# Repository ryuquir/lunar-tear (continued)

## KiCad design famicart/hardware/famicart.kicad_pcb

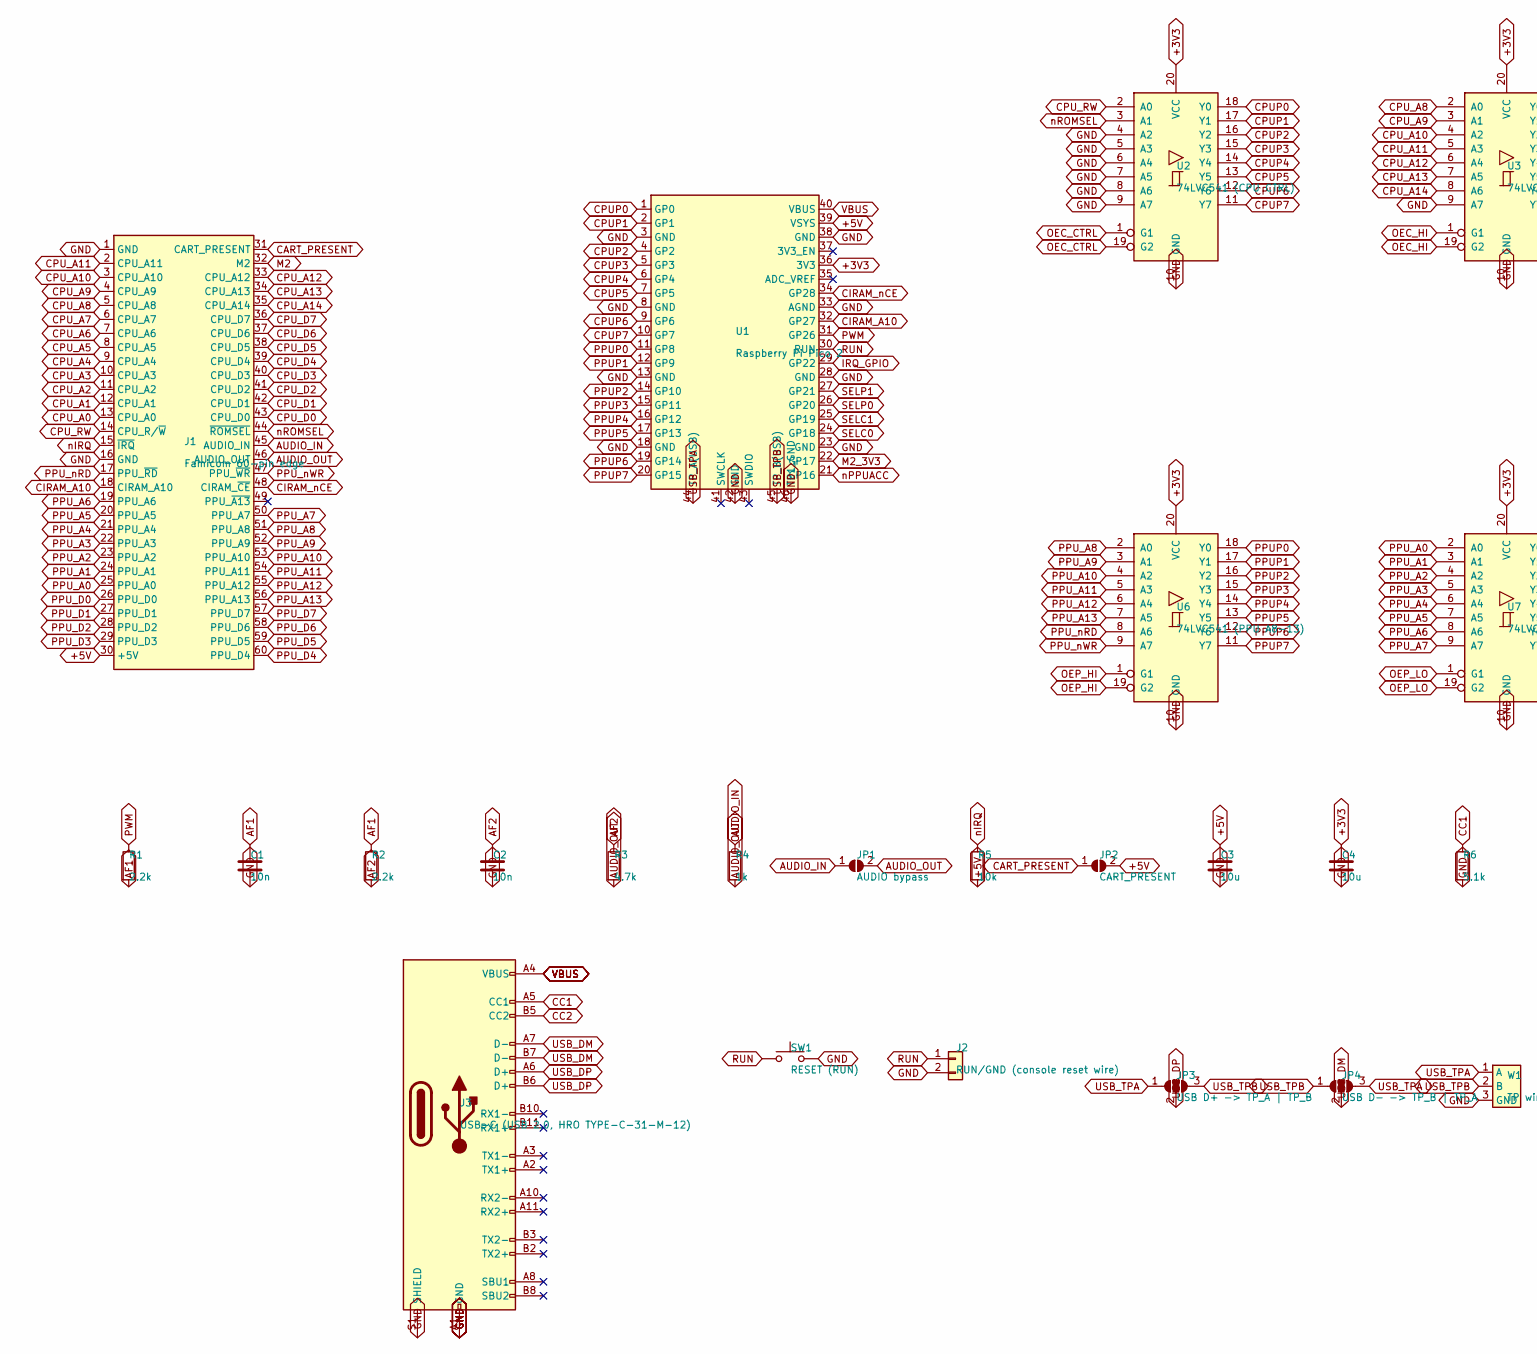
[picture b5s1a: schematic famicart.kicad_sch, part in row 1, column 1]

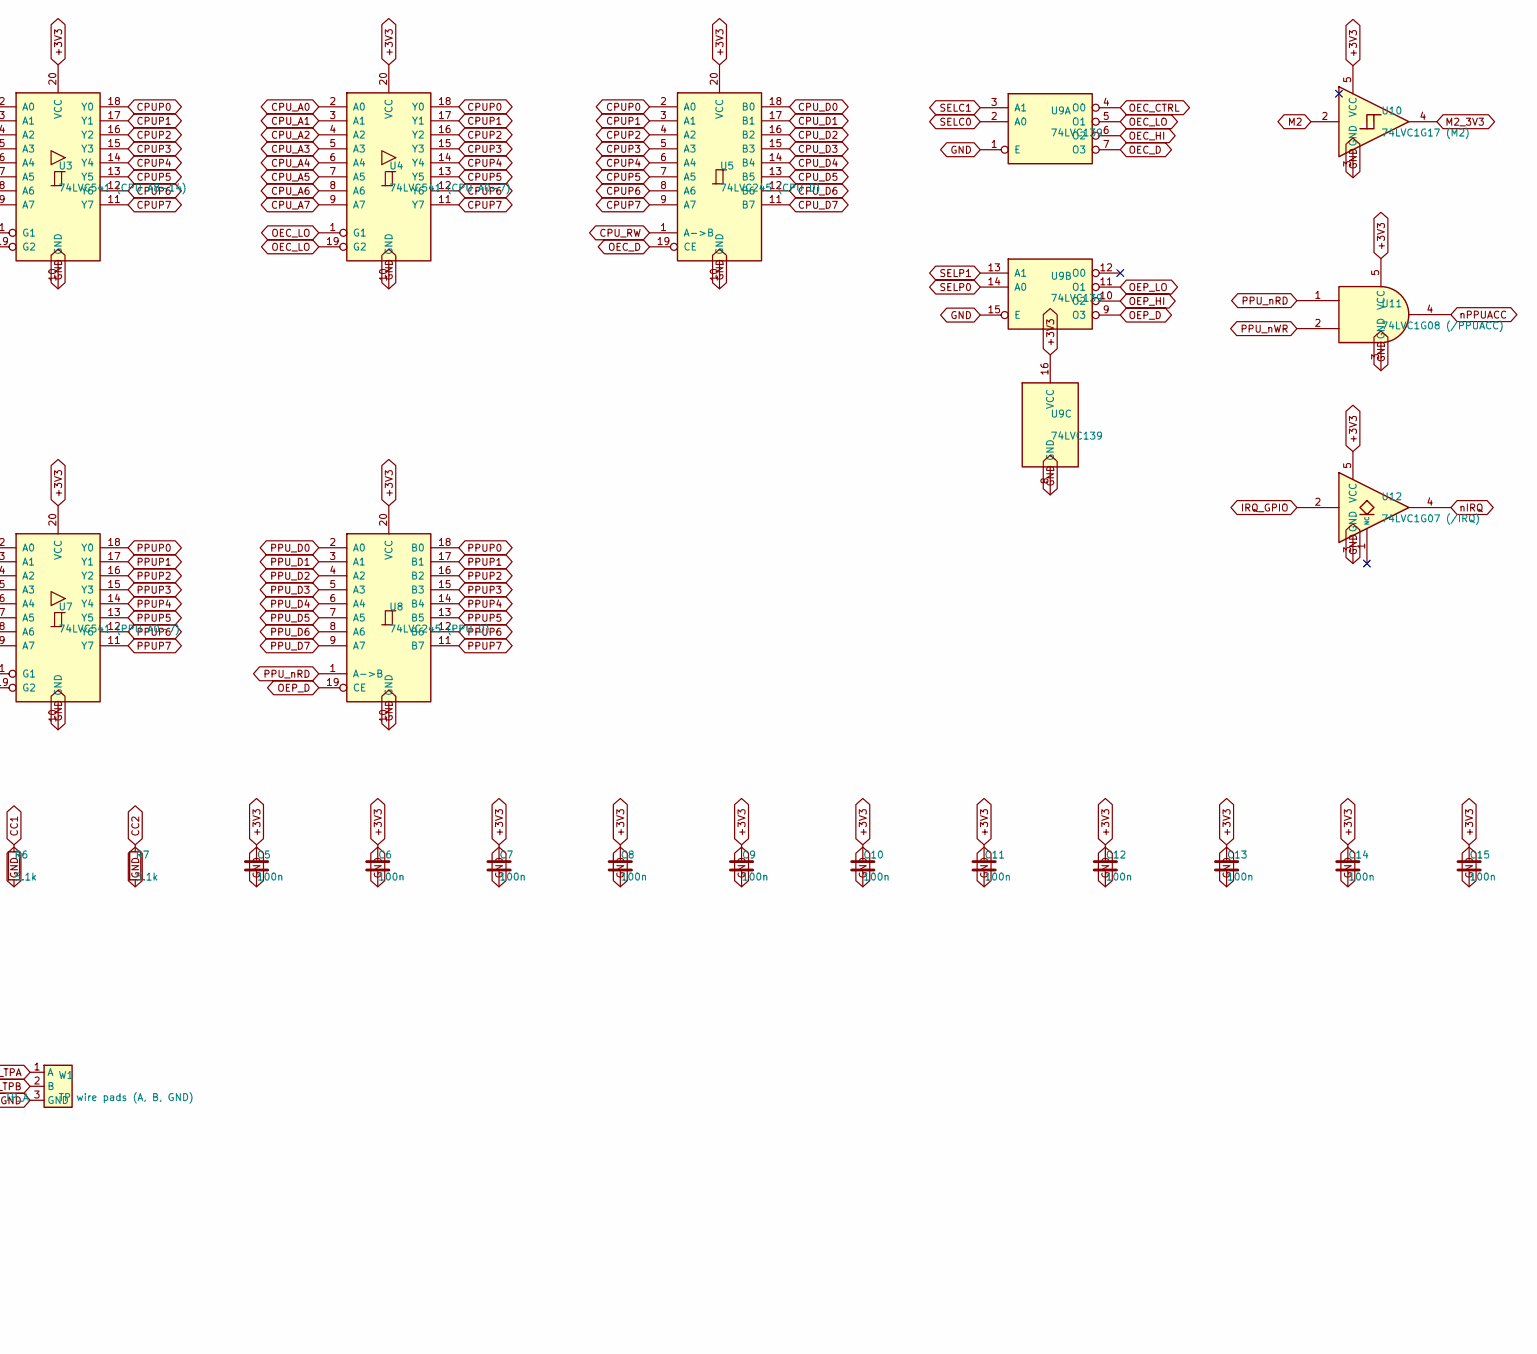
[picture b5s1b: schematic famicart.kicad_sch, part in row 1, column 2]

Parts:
C1, C2: 10n; C_0603_1608Metric
C3, C4: 10u; C_0805_2012Metric
C5, C6, C7, C8, C9, C10, C11, C12, C13, C14, C15: 100n; C_0603_1608Metric
J1: Famicom 60-pin edge; Famicom_CardEdge_60
J2: RUN/GND (console reset wire); PinHeader_1x02_P2.54mm_Vertical
J3: USB-C (USB 2.0, HRO TYPE-C-31-M-12); USB_C_Receptacle_HRO_TYPE-C-31-M-12
JP1: AUDIO bypass; SolderJumper-2_P1.3mm_Open_RoundedPad1.0x1.5mm
JP2: CART_PRESENT; SolderJumper-2_P1.3mm_Open_RoundedPad1.0x1.5mm
JP3: USB D+ -> TP_A | TP_B; SolderJumper-3_P1.6mm_Open
JP4: USB D- -> TP_B | TP_A; SolderJumper-3_P1.6mm_Open
R1, R2: 2.2k; R_0603_1608Metric
R3: 4.7k; R_0603_1608Metric
R4: 1k; R_0603_1608Metric
R5: 10k; R_0603_1608Metric
R6, R7: 5.1k; R_0603_1608Metric
SW1: RESET (RUN); SW_SPST_TL3342
U1: Raspberry Pi Pico 2; RPi_Pico_SMD
U2: 74LVC541 (CPU CTRL); TSSOP-20_4.4x6.5mm_P0.65mm
U3: 74LVC541 (CPU A8-14); TSSOP-20_4.4x6.5mm_P0.65mm
U4: 74LVC541 (CPU A0-7); TSSOP-20_4.4x6.5mm_P0.65mm
U5: 74LVC245 (CPU D); TSSOP-20_4.4x6.5mm_P0.65mm
U6: 74LVC541 (PPU A8-13); TSSOP-20_4.4x6.5mm_P0.65mm
U7: 74LVC541 (PPU A0-7); TSSOP-20_4.4x6.5mm_P0.65mm
U8: 74LVC245 (PPU D); TSSOP-20_4.4x6.5mm_P0.65mm
U9: 74LVC139; TSSOP-16_4.4x5mm_P0.65mm
U10: 74LVC1G17 (M2); SOT-23-5
U11: 74LVC1G08 (/PPUACC); SOT-23-5
U12: 74LVC1G07 (/IRQ); SOT-23-5
W1: TP wire pads (A, B, GND); WirePads_1x3

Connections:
+3V3: C4.1, C5.1, C6.1, C7.1, C8.1, C9.1, C10.1, C11.1, C12.1, C13.1, C14.1, C15.1, U1.36 (3V3), U2.20 (VCC), U3.20 (VCC), U4.20 (VCC), U5.20 (VCC), U6.20 (VCC), U7.20 (VCC), U8.20 (VCC), U9.16 (VCC), U10.5 (VCC), U11.5 (VCC), U12.5 (VCC)
+5V: C3.1, J1.30 (+5V), JP2.2 (B), R5.2, U1.39 (VSYS)
AF1: C1.1, R1.2, R2.1
AF2: C2.1, R2.2, R3.1
AUDIO_IN: J1.45 (AUDIO_IN), JP1.1 (A), R4.1
AUDIO_OUT: J1.46 (AUDIO_OUT), JP1.2 (B), R3.2, R4.2
CART_PRESENT: J1.31 (CART_PRESENT), JP2.1 (A)
CC1: J3.A5 (CC1), R6.1
CC2: J3.B5 (CC2), R7.1
CIRAM_A10: J1.18 (CIRAM_A10), U1.32 (GP27)
CIRAM_nCE: J1.48 (CIRAM_~CE), U1.34 (GP28)
CPUP0: U1.1 (GP0), U2.18 (Y0), U3.18 (Y0), U4.18 (Y0), U5.2 (A0)
CPUP1: U1.2 (GP1), U2.17 (Y1), U3.17 (Y1), U4.17 (Y1), U5.3 (A1)
CPUP2: U1.4 (GP2), U2.16 (Y2), U3.16 (Y2), U4.16 (Y2), U5.4 (A2)
CPUP3: U1.5 (GP3), U2.15 (Y3), U3.15 (Y3), U4.15 (Y3), U5.5 (A3)
CPUP4: U1.6 (GP4), U2.14 (Y4), U3.14 (Y4), U4.14 (Y4), U5.6 (A4)
CPUP5: U1.7 (GP5), U2.13 (Y5), U3.13 (Y5), U4.13 (Y5), U5.7 (A5)
CPUP6: U1.9 (GP6), U2.12 (Y6), U3.12 (Y6), U4.12 (Y6), U5.8 (A6)
CPUP7: U1.10 (GP7), U2.11 (Y7), U3.11 (Y7), U4.11 (Y7), U5.9 (A7)
CPU_A0: J1.13 (CPU_A0), U4.2 (A0)
CPU_A1: J1.12 (CPU_A1), U4.3 (A1)
CPU_A2: J1.11 (CPU_A2), U4.4 (A2)
CPU_A3: J1.10 (CPU_A3), U4.5 (A3)
CPU_A4: J1.9 (CPU_A4), U4.6 (A4)
CPU_A5: J1.8 (CPU_A5), U4.7 (A5)
CPU_A6: J1.7 (CPU_A6), U4.8 (A6)
CPU_A7: J1.6 (CPU_A7), U4.9 (A7)
CPU_A8: J1.5 (CPU_A8), U3.2 (A0)
CPU_A9: J1.4 (CPU_A9), U3.3 (A1)
CPU_A10: J1.3 (CPU_A10), U3.4 (A2)
CPU_A11: J1.2 (CPU_A11), U3.5 (A3)
CPU_A12: J1.33 (CPU_A12), U3.6 (A4)
CPU_A13: J1.34 (CPU_A13), U3.7 (A5)
CPU_A14: J1.35 (CPU_A14), U3.8 (A6)
CPU_D0: J1.43 (CPU_D0), U5.18 (B0)
CPU_D1: J1.42 (CPU_D1), U5.17 (B1)
CPU_D2: J1.41 (CPU_D2), U5.16 (B2)
CPU_D3: J1.40 (CPU_D3), U5.15 (B3)
CPU_D4: J1.39 (CPU_D4), U5.14 (B4)
CPU_D5: J1.38 (CPU_D5), U5.13 (B5)
CPU_D6: J1.37 (CPU_D6), U5.12 (B6)
CPU_D7: J1.36 (CPU_D7), U5.11 (B7)
CPU_RW: J1.14 (CPU_R/~W), U2.2 (A0), U5.1 (A->B)
GND: C1.2, C2.2, C3.2, C4.2, C5.2, C6.2, C7.2, C8.2, C9.2, C10.2, C11.2, C12.2, C13.2, C14.2, C15.2, J1.1 (GND), J1.16 (GND), J2.2, J3.A1 (GND), J3.A12 (GND), J3.B1 (GND), J3.B12 (GND), J3.S1 (SHIELD), R6.2, R7.2, SW1.2, U1.3 (GND), U1.8 (GND), U1.13 (GND), U1.18 (GND), U1.23 (GND), U1.28 (GND), U1.33 (AGND), U1.38 (GND), U1.42 (GND), U1.46 (TP1_GND), U2.4 (A2), U2.5 (A3), U2.6 (A4), U2.7 (A5), U2.8 (A6), U2.9 (A7), U2.10 (GND), U3.9 (A7), U3.10 (GND), U4.10 (GND), U5.10 (GND), U6.10 (GND), U7.10 (GND), U8.10 (GND), U9.1 (E), U9.8 (GND), U9.15 (E), U10.3 (GND), U11.3 (GND), U12.3 (GND), W1.3 (GND)
IRQ_GPIO: U1.29 (GP22), U12.2
M2: J1.32 (M2), U10.2
M2_3V3: U1.22 (GP17), U10.4
OEC_CTRL: U2.1 (G1), U2.19 (G2), U9.4 (O0)
OEC_D: U5.19 (CE), U9.7 (O3)
OEC_HI: U3.1 (G1), U3.19 (G2), U9.6 (O2)
OEC_LO: U4.1 (G1), U4.19 (G2), U9.5 (O1)
OEP_D: U8.19 (CE), U9.9 (O3)
OEP_HI: U6.1 (G1), U6.19 (G2), U9.10 (O2)
OEP_LO: U7.1 (G1), U7.19 (G2), U9.11 (O1)
PPUP0: U1.11 (GP8), U6.18 (Y0), U7.18 (Y0), U8.18 (B0)
PPUP1: U1.12 (GP9), U6.17 (Y1), U7.17 (Y1), U8.17 (B1)
PPUP2: U1.14 (GP10), U6.16 (Y2), U7.16 (Y2), U8.16 (B2)
PPUP3: U1.15 (GP11), U6.15 (Y3), U7.15 (Y3), U8.15 (B3)
PPUP4: U1.16 (GP12), U6.14 (Y4), U7.14 (Y4), U8.14 (B4)
PPUP5: U1.17 (GP13), U6.13 (Y5), U7.13 (Y5), U8.13 (B5)
PPUP6: U1.19 (GP14), U6.12 (Y6), U7.12 (Y6), U8.12 (B6)
PPUP7: U1.20 (GP15), U6.11 (Y7), U7.11 (Y7), U8.11 (B7)
PPU_A0: J1.25 (PPU_A0), U7.2 (A0)
PPU_A1: J1.24 (PPU_A1), U7.3 (A1)
PPU_A2: J1.23 (PPU_A2), U7.4 (A2)
PPU_A3: J1.22 (PPU_A3), U7.5 (A3)
PPU_A4: J1.21 (PPU_A4), U7.6 (A4)
PPU_A5: J1.20 (PPU_A5), U7.7 (A5)
PPU_A6: J1.19 (PPU_A6), U7.8 (A6)
PPU_A7: J1.50 (PPU_A7), U7.9 (A7)
PPU_A8: J1.51 (PPU_A8), U6.2 (A0)
PPU_A9: J1.52 (PPU_A9), U6.3 (A1)
PPU_A10: J1.53 (PPU_A10), U6.4 (A2)
PPU_A11: J1.54 (PPU_A11), U6.5 (A3)
PPU_A12: J1.55 (PPU_A12), U6.6 (A4)
PPU_A13: J1.56 (PPU_A13), U6.7 (A5)
PPU_D0: J1.26 (PPU_D0), U8.2 (A0)
PPU_D1: J1.27 (PPU_D1), U8.3 (A1)
PPU_D2: J1.28 (PPU_D2), U8.4 (A2)
PPU_D3: J1.29 (PPU_D3), U8.5 (A3)
PPU_D4: J1.60 (PPU_D4), U8.6 (A4)
PPU_D5: J1.59 (PPU_D5), U8.7 (A5)
PPU_D6: J1.58 (PPU_D6), U8.8 (A6)
PPU_D7: J1.57 (PPU_D7), U8.9 (A7)
PPU_nRD: J1.17 (PPU_~RD), U6.8 (A6), U8.1 (A->B), U11.1
PPU_nWR: J1.47 (PPU_~WR), U6.9 (A7), U11.2
PWM: R1.1, U1.31 (GP26)
RUN: J2.1, SW1.1, U1.30 (RUN)
SELC0: U1.24 (GP18), U9.2 (A0)
SELC1: U1.25 (GP19), U9.3 (A1)
SELP0: U1.26 (GP20), U9.14 (A0)
SELP1: U1.27 (GP21), U9.13 (A1)
USB_DM: J3.A7 (D-), J3.B7 (D-), JP4.2 (C)
USB_DP: J3.A6 (D+), J3.B6 (D+), JP3.2 (C)
USB_TPA: JP3.1 (A), JP4.3 (B), U1.44 (TP_A(USB)), W1.1 (A)
USB_TPB: JP3.3 (B), JP4.1 (A), U1.45 (TP_B(USB)), W1.2 (B)
VBUS: J3.A4 (VBUS), J3.A9 (VBUS), J3.B4 (VBUS), J3.B9 (VBUS), U1.40 (VBUS)
nIRQ: J1.15 (~IRQ), R5.1, U12.4
nPPUACC: U1.21 (GP16), U11.4
nROMSEL: J1.44 (~ROMSEL), U2.3 (A1)

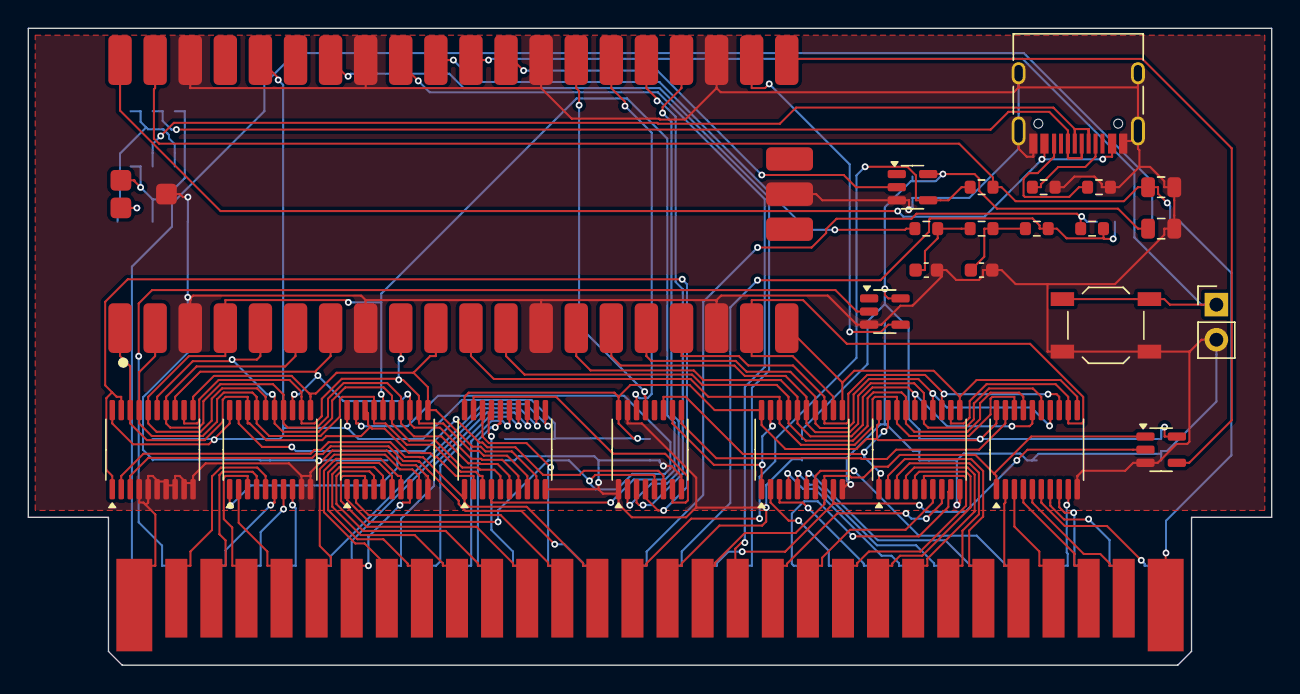
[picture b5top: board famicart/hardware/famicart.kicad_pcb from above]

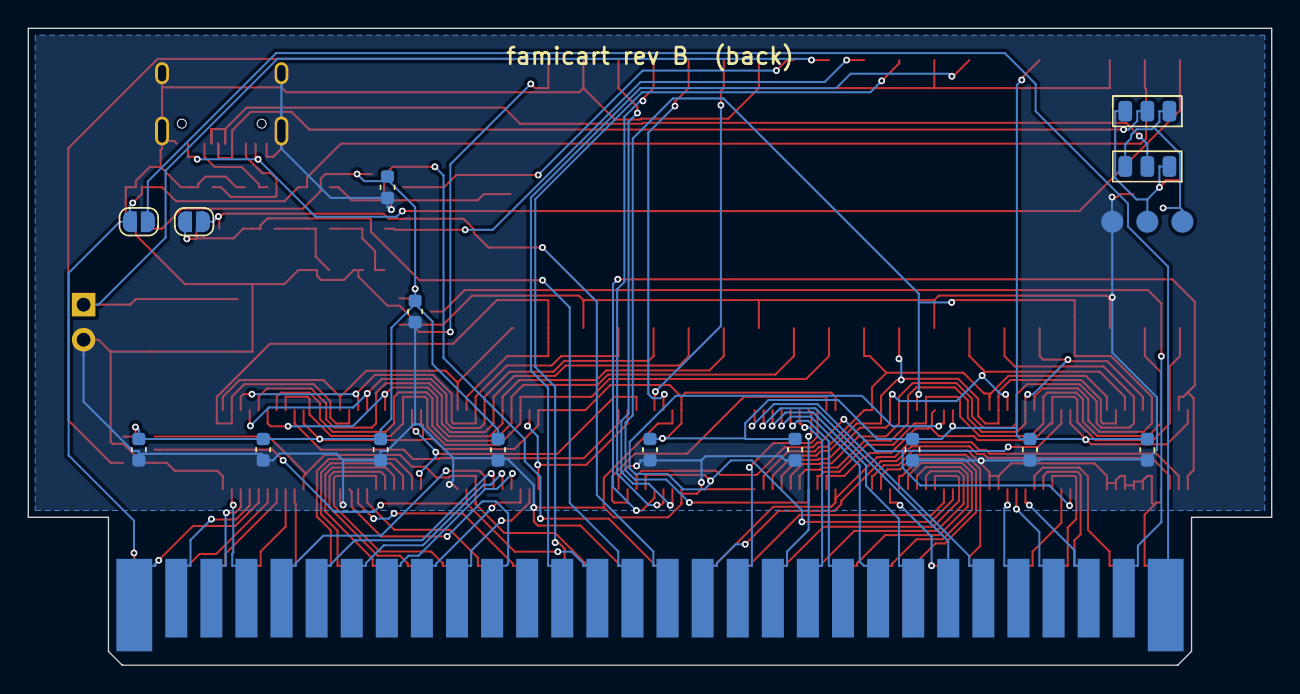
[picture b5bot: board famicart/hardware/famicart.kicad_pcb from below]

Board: 2 copper layers, 90.0 x 46.1 mm, 43 parts (16 on the bottom side), 100 nets.

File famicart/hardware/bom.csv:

Qty,Value,Footprint,References,Suggested part
1,Famicom 60-pin edge,Famicom_CardEdge_60,J1,"PCB card edge (gold fingers), no part"
1,Raspberry Pi Pico 2,RPi_Pico_SMD,U1,Raspberry Pi SC1631 (Pico 2) / Pico (RP2040) also fits
5,74LVC541,TSSOP-20_4.4x6.5mm_P0.65mm,U2 U3 U4 U6 U7,Nexperia 74LVC541APW (TSSOP-20)
2,74LVC245,TSSOP-20_4.4x6.5mm_P0.65mm,U5 U8,Nexperia 74LVC245APW (TSSOP-20)
1,74LVC139,TSSOP-16_4.4x5mm_P0.65mm,U9,Nexperia 74LVC139PW (TSSOP-16)
1,74LVC1G17,SOT-23-5,U10,Nexperia 74LVC1G17GW / TI SN74LVC1G17DBV
1,USB-C,USB_C_Receptacle_HRO_TYPE-C-31-M-12,J3,HRO TYPE-C-31-M-12 (16-pin USB 2.0 receptacle) or GCT USB4105-GF-A
2,5.1k,R_0603_1608Metric,R6 R7,0603 1% (USB-C CC pull-down)
1,USB D+ -> TP_A | TP_B,SolderJumper-3_P1.6mm_Open,JP3,"solder jumper, bridge after checking TP2/TP3"
1,USB D- -> TP_B | TP_A,SolderJumper-3_P1.6mm_Open,JP4,"solder jumper, bridge after checking TP2/TP3"
1,TP wire pads,WirePads_1x3,W1,no part (solder wires from Pico TP2/TP3/TP1 if hand-assembling)
1,RESET,SW_SPST_TL3342,SW1,E-Switch TL3342 / any 4.7x3.5 mm low-profile tactile
1,RUN/GND,PinHeader_1x02_P2.54mm_Vertical,J2,"2-pin 2.54 mm header (optional, wire to the console reset switch)"
1,74LVC1G08,SOT-23-5,U11,Nexperia 74LVC1G08GW / TI SN74LVC1G08DBV
1,74LVC1G07,SOT-23-5,U12,Nexperia 74LVC1G07GW / TI SN74LVC1G07DBV
2,2.2k,R_0603_1608Metric,R1 R2,0603 1%
1,4.7k,R_0603_1608Metric,R3,0603 1%
1,1k,R_0603_1608Metric,R4,0603 1%
1,10k,R_0603_1608Metric,R5,0603 1%
2,10n,C_0603_1608Metric,C1 C2,X7R 0603 50V
2,10u,C_0805_2012Metric,C3 C4,X5R 0805 10V
1,AUDIO bypass,SolderJumper-2_P1.3mm_Open_RoundedPad1.0x1.5mm,JP1,
1,CART_PRESENT,SolderJumper-2_P1.3mm_Open_RoundedPad1.0x1.5mm,JP2,
11,100n,C_0603_1608Metric,C5 C6 C7 C8 C9 C10 C11 C12 C13 C14 C15,X7R 0603 16V

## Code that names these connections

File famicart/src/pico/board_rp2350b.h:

/* famicart rev C: bare RP2350B, all 48 GPIO used, console signals connected directly (RP2350 GPIO are 5 V tolerant).
 *
 *  GPIO0-14  CPU A0-A14      GPIO15-22 CPU D0-D7      GPIO23 R/W   GPIO24 M2   GPIO25 /ROMSEL   GPIO26 /IRQ (emulated open drain)
 *  GPIO27    CIRAM /CE       GPIO28/29 UART0 TX/RX -> XIAO RP2040 (audio coprocessor)
 *  GPIO30-37 PPU shared port (A0-7 via 74LVC541 while PPU_SEL=0, D0-7 via 74LVC245 while PPU_SEL=1)
 *  GPIO38-43 PPU A8-A13      GPIO44 /PPUACC (= /RD & /WR)   GPIO45 PPU /RD   GPIO46 PPU_SEL   GPIO47 CIRAM A10
 */
#pragma once
#define FC_BUS_CAPABLE        1
#define FC_BUS_DIRECT         1      /* CPU bus wired directly: one 26-bit PIO capture per M2 */
#define FC_AUDIO_REMOTE       1      /* expansion-audio registers are streamed to the XIAO over UART0 */

#define PIN_CPU_BASE          0      /* GPIO0..25: A0-14 (0-14), D0-7 (15-22), R/W 23, M2 24, /ROMSEL 25 */
#define PIN_CPU_DATA_BASE     15
#define PIN_CPU_RW            23
#define PIN_CPU_M2            24
#define PIN_CPU_ROMSEL        25
#define PIN_IRQ               26
#define PIN_CIRAM_CE          27
#define PIN_UART_TX           28
#define PIN_UART_RX           29
#define PIN_PPU_PORT_BASE     30     /* GPIO30..45 captured in one go: port(8) A8-13(6) /PPUACC /RD */
#define PIN_PPU_AHI_BASE      38
#define PIN_PPU_ACC           44
#define PIN_PPU_RD            45
#define PIN_PPU_SEL           46
#define PIN_CIRAM_A10         47
#define PIN_AUDIO_PWM         (-1)   /* audio is produced by the XIAO */

#define FC_SYS_CLOCK_KHZ      300000 /* RP2350 overclock; 150 MHz nominal also works with less margin */
#define FC_FLASH_ROM_SLOT     0x00100000u   /* 1 MiB into the 16 MiB flash */
#define FC_FLASH_ROM_SLOT_MAX 0x00F00000u   /* 15 MiB: room for a ROM library (phase 3) */

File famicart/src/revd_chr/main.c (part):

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static cart_t cart; static bool loaded; static uint32_t chr_base_bank;
static volatile bool live;                 /* false: boot state (CHR bank 0, H mirroring) */

/* ---- bank words: GPIO16-31 = CHR A10-A25 (gpio_out bits 16..31); GPIO32 SEL, 33 nFOURSCR, 34 CIRAM_A10 (gpio_hi_out bits 0..2) ---- */
static volatile uint32_t w_lo[16], w_hi[16];   /* index = PPU A10-A13 */
#define LO_MASK 0xFFFF0000u
#define HI_MASK 0x7u
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            if (lo != cur_lo) { sio_hw->gpio_togl = lo ^ cur_lo; cur_lo = lo; }
            if (hi != cur_hi) { sio_hw->gpio_hi_togl = hi ^ cur_hi; cur_hi = hi; }
        }
        bool rd = (in >> PIN_PPU_NRD) & 1;
        if (!rd && rd_prev && loaded && cart.has_ppu_hook) {
            cart.ppu_override = NULL; cart.mapper->ppu_addr(&cart, (uint16_t)(in & 0x3FFF));
            if (cart.tables_dirty) encode_all(&cart);
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    }
}

/* ---- programming agent: U2 drives PA0-13, PnRD, PnWR, CHR_nWE, bank lines; U1 drives data via the bridge ---- */
static bool prog_mode; static uint32_t prog_addr; static bool prog_ram;
static void prog_set(bool on) {
    prog_mode = on;
    if (on) {
        multicore_reset_core1();
        for (uint g = 0; g < 14; g++) { gpio_set_dir(g, true); gpio_put(g, 0); }
        gpio_set_dir(PIN_PPU_NRD, true); gpio_put(PIN_PPU_NRD, 1); gpio_set_dir(PIN_PPU_NWR, true); gpio_put(PIN_PPU_NWR, 1);
        gpio_put(PIN_NBRIDGE, 0); gpio_put(PIN_BRIDGE_DIR, 1);
    } else {
        gpio_put(PIN_PPU_NRD, 1); gpio_put(PIN_PPU_NWR, 1); gpio_put(PIN_NBRIDGE, 1); gpio_put(PIN_BRIDGE_DIR, 1);
        for (uint g = 0; g < 16; g++) gpio_set_dir(g, false);
        multicore_launch_core1(ppu_core1);
    }
}
static inline void dly(unsigned n) { while (n--) __asm volatile("nop"); }
static void prog_apply_addr(void) {
    /* PA0-9 = addr & 0x3FF (PA10-13 stay 0 so A13=0 => cart region), bank lines = addr >> 10, SEL = ram */
    sio_hw->gpio_togl = (sio_hw->gpio_out ^ ((prog_addr & 0x3FF) | ((prog_addr >> 10) << 16))) & (0x3FFu | LO_MASK);
    sio_hw->gpio_hi_togl = (sio_hw->gpio_hi_out ^ (prog_ram ? HI_SEL : 0)) & HI_SEL;
}
static void prog_write_pulse(void) {
    prog_apply_addr(); gpio_put(PIN_BRIDGE_DIR, 1); dly(4);
    gpio_put(PIN_PPU_NWR, 0); dly(3);                /* PPU_ACC -> /CART_ACC -> chip /CE */
    gpio_put(PIN_CHR_NWE, 0); dly(8); gpio_put(PIN_CHR_NWE, 1); dly(2);
    gpio_put(PIN_PPU_NWR, 1);
}
static void prog_read_begin(void) { prog_apply_addr(); gpio_put(PIN_BRIDGE_DIR, 0); dly(2); gpio_put(PIN_PPU_NRD, 0); dly(20); }
static void prog_read_end(void) { gpio_put(PIN_PPU_NRD, 1); dly(2); gpio_put(PIN_BRIDGE_DIR, 1); }

/* ---- LOAD blob from U1 ---- */
static uint8_t blob[sizeof(rom_info_t) + sizeof(cart_profile_t) + 16]; static uint32_t blob_len, blob_fill;
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    set_sys_clock_khz(FC_SYS_CLOCK_KHZ, true);
    for (uint g = PIN_CHR_BANK_BASE; g < PIN_CHR_BANK_BASE + PIN_CHR_BANK_BITS; g++) { gpio_init(g); gpio_set_dir(g, true); gpio_put(g, 0); gpio_set_slew_rate(g, GPIO_SLEW_RATE_FAST); }
    for (uint g = 0; g < 16; g++) { gpio_init(g); gpio_set_dir(g, false); gpio_set_input_hysteresis_enabled(g, true); }
    const uint outs[] = { PIN_CHR_SEL, PIN_NFOURSCR, PIN_CIRAM_A10, PIN_LED, PIN_CHR_NWE, PIN_IRQ, PIN_NBRIDGE, PIN_BRIDGE_DIR };
    for (unsigned i = 0; i < sizeof outs / sizeof outs[0]; i++) { gpio_init(outs[i]); gpio_set_dir(outs[i], true); }
    gpio_put(PIN_CHR_SEL, 0); gpio_put(PIN_NFOURSCR, 1); gpio_put(PIN_CHR_NWE, 1); gpio_put(PIN_IRQ, 1); gpio_put(PIN_NBRIDGE, 1); gpio_put(PIN_BRIDGE_DIR, 1);
    gpio_init(PIN_CHR_RYBY); gpio_set_dir(PIN_CHR_RYBY, false); gpio_pull_up(PIN_CHR_RYBY);
    encode_boot();
    maplink_init();
    multicore_launch_core1(ppu_core1);
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
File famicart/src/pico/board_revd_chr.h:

/* famicart rev D, U2 "CHR mapper" (RP2350B): snoops the local PPU bus, drives CHR flash/RAM bank lines,
 * CHR ROM/RAM select, CIRAM A10 and the 4-screen enable; runs the PPU-side mapper hooks (MMC2/MMC4 latches,
 * MMC3 A12 counter, MMC5 scanline counter) and raises /IRQ_B. State arrives from U1 over the 2-wire link. */
#pragma once
#define FC_BUS_CAPABLE        0
#define FC_VIRTUAL_ROM        1
#define FC_ROLE_CHR           1

#define PIN_PPU_BASE          0      /* GPIO0-13 = PA0-13 */
#define PIN_PPU_NRD           14
#define PIN_PPU_NWR           15
#define PIN_CHR_BANK_BASE     16     /* GPIO16-31 = CHR flash / CHR RAM A10-A25 */
#define PIN_CHR_BANK_BITS     16
#define PIN_CHR_SEL           32     /* 0 = CHR flash, 1 = CHR RAM */
#define PIN_NFOURSCR          33     /* 0 = CIRAM disabled (4-screen / mapper nametables in CHR RAM) */
#define PIN_CIRAM_A10         34
#define PIN_LED               35
#define PIN_CHR_NWE           36
#define PIN_LINK_CLK          37     /* <- U1 */
#define PIN_LINK_DATA         38     /* <- U1 */
#define PIN_LINK_TX           39     /* -> U1 (PIO UART, 2 Mbaud) */
#define PIN_IRQ               40
#define PIN_NBRIDGE           41     /* low: CPU<->PPU data bridge enabled (flash programming / read-back) */
#define PIN_BRIDGE_DIR        42     /* 1: CPU->PPU, 0: PPU->CPU */
#define PIN_CHR_RYBY          43     /* CHR flash RY/BY# */
#define PIN_AUDIO_PWM         (-1)
#define PIN_CIRAM_CE          (-1)
#define PIN_UART_TX           (-1)

#define FC_SYS_CLOCK_KHZ      150000
#define FC_FLASH_ROM_SLOT     0x00100000u
#define FC_FLASH_ROM_SLOT_MAX 0x00010000u

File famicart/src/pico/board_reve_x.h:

/* famicart rev E, U3: Seeed XIAO RP2350 "special chip" -- IRQ timing and expansion audio.
 *   D0 = GPIO26 LINK   D1 = GPIO27 audio PWM (RC to AUDIO_OUT)   D2 = GPIO28 IRQ gate (2N7002 -> /IRQ, high = assert)
 *   D3 = GPIO5 M2 (1 k)   D4 = GPIO6 PPU A12   D5 = GPIO7 PPU A13   D6 = GPIO0 PPU /RD */
#pragma once
#define FC_BUS_CAPABLE        0
#define FC_REVE               1
#define PIN_LINK              26
#define PIN_AUDIO_PWM         27
#define PIN_IRQ_GATE          28
#define PIN_M2                5
#define PIN_PA12              6
#define PIN_PA13              7
#define PIN_PPU_RD            0
#define PIN_LED               25
#define PIN_UART_TX           (-1)
#define PIN_CIRAM_A10         (-1)
#define PIN_CIRAM_CE          (-1)
#define FC_SYS_CLOCK_KHZ      240000
#define FC_FLASH_ROM_SLOT     0x00100000u

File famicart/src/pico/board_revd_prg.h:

/* famicart rev D, U1 "PRG mapper / expansion chip" (RP2350B). Sits on the 3.3 V local bus; the PRG flash and the
 * F-RAM answer the console directly, this MCU only drives their bank/select lines, serves $4020-$5FFF itself
 * and runs the expansion-audio synth. */
#pragma once
#define FC_BUS_CAPABLE        0      /* bus.c (rev A-C data-serving front-ends) compiled out; bus_revd.c instead */
#define FC_BUS_REVD           1
#define FC_VIRTUAL_ROM        1
#define FC_ROLE_PRG           1

#define PIN_CPU_BASE          0      /* GPIO0-25: CA0-14, CD0-7, CRW, CM2, CnROMSEL (same order as rev C) */
#define PIN_CPU_DATA_BASE     15
#define PIN_CPU_RW            23
#define PIN_CPU_M2            24
#define PIN_CPU_ROMSEL        25
#define PIN_NDRIVE            26     /* low: our data reaches the console (74LVC245 enable) */
#define PIN_PRG_BANK_BASE     27     /* GPIO27-39 = PRG flash / F-RAM A13-A25 */
#define PIN_PRG_BANK_BITS     13
#define PIN_WRAM_NCE          40
#define PIN_IRQ               41     /* through a 74LVC1G07 open-drain buffer */
#define PIN_AUDIO_PWM         42
#define PIN_LINK_CLK          43     /* -> U2 */
#define PIN_LINK_DATA         44     /* -> U2 */
#define PIN_LINK_RX           45     /* <- U2 (PIO UART, 2 Mbaud) */
#define PIN_PRG_NWE           46
#define PIN_ISOLATE           47     /* high: all 74LVC541/245 towards the console disabled */
#define PIN_CIRAM_A10         (-1)
#define PIN_CIRAM_CE          (-1)
#define PIN_UART_TX           (-1)

#define FC_SYS_CLOCK_KHZ      150000
#define FC_FLASH_ROM_SLOT     0x00100000u   /* U1 QSPI: ROM library index (not the ROM itself) */
#define FC_FLASH_ROM_SLOT_MAX 0x00100000u
#define FC_BOOT_BANK          0x1FFFu       /* top 8 KB bank of the 64 MB PRG flash = boot stub */

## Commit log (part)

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2026-03-16 [major, quest flow fix]
2026-03-17 Refactor Gacha and Scene Management in README and Code
    - Updated README to reflect changes in bootstrap options, replacing `--bootstrap-profile` with `--scene` for user initialization.
    - Refactored main.go to accommodate the new scene-based bootstrapping, enhancing user state management.
    - Adjusted Gacha catalog loading and related functions to ensure consistency with updated identifiers and improve clarity in asset resolution.
    - Removed obsolete functions and variables related to Gacha and quest handling, streamlining the codebase for better maintainability.
2026-03-18 Remove mock package and enhance quest flow engine with new scene and costume management
    - Deleted the mock package as it was no longer needed.
    - Introduced new types for scene grants and costumes in the quest flow engine to improve data handling.
    - Updated the engine to apply scene grants during quest progress, enhancing user experience.
    - Modified user state to include weapon notes and ensure comprehensive updates across user interactions.
2026-03-19 Update .gitignore and remove empty .keep file in frida directory
    - Added 'frida/' to .gitignore to exclude the frida directory from version control.
    - Deleted the empty .keep file in the frida directory to clean up the project structure.
2026-03-19 Refactor Quest Handling and Improve Logging
    - Updated ApplyBootstrap method to replace panic with a fatal log for unknown scene IDs, enhancing error handling.
    - Modified HandleQuestFinish method to include an isRetired parameter, improving quest completion logic.
    - Added new user data types (IUserConsumableItem, IUserMaterial, IUserImportantItem) to various service components for better state management.
    - Cleaned up state projection by removing unused user data types, streamlining data representation.
2026-03-20 Add Tutorial Unlock Conditions and Update User State Management
    - Introduced tutorialUnlockCondition struct to manage tutorial unlock criteria, enhancing tutorial progression logic.
    - Updated Engine to load tutorial unlock conditions from JSON, improving initialization of tutorial states.
    - Refactored UserState to use a map for storing multiple tutorial progress states, allowing for better management of user tutorials.
    - Enhanced state projection to sort and represent tutorial progress accurately, ensuring comprehensive user data handling.
2026-03-22 Enhance Quest Flow with Battle Drop Rewards
    - Updated the quest engine to include battle drop rewards, allowing for dynamic reward allocation based on quest completion.
    - Modified the StartMainQuest and FinishMainQuest methods to return battle drop rewards in the response, improving user feedback during quest progression.
    - Introduced new data structures for managing battle drop rewards and pickup reward groups, enhancing the overall quest reward system.
2026-03-22 Refactor Server into Domain-Oriented Architecture
    - Extract repository interfaces (UserRepository, SessionRepository,
    GachaRepository) from monolithic store.go; move MemoryStore to
    store/memory/ sub-package with error returns for DB compatibility
    - Split questflow/engine.go (1451 lines) into engine, rewards, battle,
    bootstrap, scene files
    - Replace monolithic state_projection.go with table-driven projector
2026-03-24 Enhance Main Quest Scene Progress Handling
    - Added logic to determine if the user has reached the last quest scene, updating MainQuest.IsReachedLastQuestScene accordingly.
    - Updated user portal cage status to reflect current progress and latest version during scene progress handling.
    - Adjusted user data diff to include IUserPortalCageStatus and IUserQuest, improving state management during quest updates.
2026-03-25 Add Snapshot Management for User State
    - Introduced snapshot functionality to save and load user state based on the current quest scene.
    - Updated MemoryStore to handle snapshot directory and scene ID during user state updates.
    - Enhanced user state initialization to load from snapshots if available, improving user experience during quest progression.
    - Added new methods for saving and loading snapshots in memory store, ensuring persistent user state across sessions.
    - Updated .gitignore to exclude snapshot files from version control.
2026-03-25 Implement Character Viewer Feature
    - Added CharacterViewer service to manage character viewing functionality.
    - Introduced CharacterViewerCatalog to handle character viewer fields and their release conditions.
    - Updated gRPC server to register the new CharacterViewer service and its dependencies.
    - Modified Makefile to include the new proto file for character viewer.
    - Enhanced main application entry point to initialize the character viewer catalog.
    - Implemented logic for retrieving released character viewer fields based on user quest state.
2026-03-28 Update CHANGELOG with new features and enhancements for 2026-03-28
2026-03-29 Add Fast Purchase Methods to IAP Patching
    - Updated `patch_apk.py` to include new methods for fast purchasing, allowing users to skip certain checks during in-app purchases.
    - Added patches to bypass the `CheckPurchasingAlert` and `_initialized` checks, improving the efficiency of the purchasing process.
    - Modified the patching output message to reflect the inclusion of fast purchase functionality.
2026-04-02 Add Weapon Management Features
    - Introduced WeaponService to handle weapon enhancements, including material consumption and experience tracking.
    - Added support for weapon skills and abilities in user state, allowing for detailed weapon management.
    - Implemented loading and cataloging of weapon data, including enhancements and experience thresholds.
    - Updated gRPC server to register the new WeaponService and its associated methods.
    - Enhanced user data projections to include weapon skills and abilities, improving client-side data handling.
2026-04-02 Add shared ConditionResolver and GimmickCatalog for server-side gimmick data
    Extract evaluate-condition logic into a reusable ConditionResolver, refactor
    CharacterViewerCatalog to use it, and add GimmickCatalog that populates
    IUserGimmickSequence entries in InitSequenceSchedule based on active schedules.
2026-04-03 Add Mythic Slab Features
    - Introduced CharacterBoardCatalog and CharacterBoardService to manage character board data, including panel releases and status effects.
    - Implemented loading and handling of character board data from JSON files, enhancing user experience with character board interactions.
    - Updated user state to include character board abilities and status ups, improving tracking of user progress and character enhancements.
    - Registered new user data projections for character boards, ensuring accurate client-side representation of character board states.
    - Modified gRPC server to register the new CharacterBoardService and its associated methods, integrating it into the existing ser
2026-04-04 Add Memoir Reward Features
    - Introduced PartsRow structure to manage parts data, including IDs and lottery group associations.
    - Updated QuestCatalog to load and index parts data, enhancing quest-related functionalities.
    - Enhanced user state to include PartsGroupNotes for tracking parts acquisition and status.
    - Implemented logic in QuestHandler to manage parts rewards and user state updates, improving user experience.
    - Registered new user data projections for parts and parts group notes, ensuring accurate client-side representation.
2026-04-04 Add Costume Awakening Features
    - Introduced new data structures for costume awakening, including CostumeAwakenRow, CostumeAwakenEffectRow, and related types to manage awakening effects and item acquisition.
    - Enhanced CostumeCatalog to support awakening data, allowing for dynamic loading and management of awakening-related information.
    - Implemented awakening logic in CostumeService, enabling users to awaken costumes with associated effects and status updates.
    - Updated user state to track costume awakening status, ensuring accurate representation of user progress and effects.
    - Enhanced data projection for costume awakening status, improving client-side synchronization and representation of
2026-04-04 Add Shop Catalog Enhancements
    - Introduced new data structures for shop management, including shopRow, shopItemCellGroupRow, and shopItemCellRow to facilitate item organization.
    - Implemented loading of shop data from JSON files, enhancing the ShopCatalog with an ItemShopPool for dynamic item management.
    - Updated user state handling in ShopServiceServer to incorporate the new item shop pool, improving user experience with replaceable shop items.
    - Enhanced sorting logic for item display in the shop, ensuring items are presented in a user-friendly order.
2026-04-05 Add Sell RPCs for Material, Parts, and Weapon services with DeleteTracker
    Implement MaterialService/Sell, PartsService/Sell, and WeaponService/Sell
    RPCs. Introduce DeleteTracker to properly send DeleteKeysJson when items
    are removed from user state, and apply it to existing Rebirth and
    ReleasePanel handlers as well.
2026-04-06 Enhance Weapon Story Unlock Logic in QuestHandler
    - Updated grantWeapon method to handle multiple weapon story release conditions, including acquisition and quest clear types.
    - Implemented logic to grant weapon story unlocks based on quest completion state, improving user experience with weapon rewards.
2026-04-06 Enhance Weapon Skill and Ability Management in WeaponService
    - Introduced new data structures for weapon skill and ability enhancement, including WeaponSkillEnhanceMaterialRow and WeaponAbilityEnhanceMaterialRow, to support skill and ability upgrades.
    - Updated WeaponCatalog to include mappings for skill and ability enhancement materials, improving organization and access to related data.
    - Implemented EnhanceSkill and EnhanceAbility methods in WeaponServiceServer to handle skill and ability enhancement logic, including material cost deduction and level management.
    - Enhanced logging for skill and ability enhancement processes to improve traceability and user experience.
2026-04-07 Add MainQuestRouteRow Structure and Enhance Quest Handling Logic
    - Introduced MainQuestRouteRow structure to manage quest route data, including MainQuestRouteId, MainQuestSeasonId, SortOrder, and CharacterId.
    - Updated LoadQuestCatalog function to read and process main quest route data, mapping season IDs by route IDs for improved quest management.
    - Enhanced HandleQuestStart method to set MainQuestSeasonId based on the route ID, improving user state management during quest flow.
    - Added SetRoute method in QuestServiceServer to update user quest route and season ID, ensuring accurate tracking of user progress.
2026-04-09 Implement Deck Skins Support
2026-04-10 Enhance Gacha Pool Logic and Exclude Evolved Weapons
    - Added functionality to load weapon evolution group data and build a set of evolved weapons to be excluded from the gacha pool.
    - Refactored gacha pool item selection logic to skip evolved weapons, improving the integrity of the gacha draw process.
    - Updated logging to provide insights on the number of excluded evolved weapons, enhancing traceability in gacha operations.
    - Utilized the 'slices' package for sorting weapon IDs, streamlining the sorting process in the gacha pool logic.
2026-04-10 Implement Big Hunt service
    Add BigHuntService with all RPCs (start, finish, restart, skip, save
    battle info, get top data), reward service, master data catalog, user
    state, and client projections. Create dedicated Big Hunt quest handlers
    to avoid corrupting main quest state.
2026-04-13 Update README with legal disclaimer and asset usage warnings
